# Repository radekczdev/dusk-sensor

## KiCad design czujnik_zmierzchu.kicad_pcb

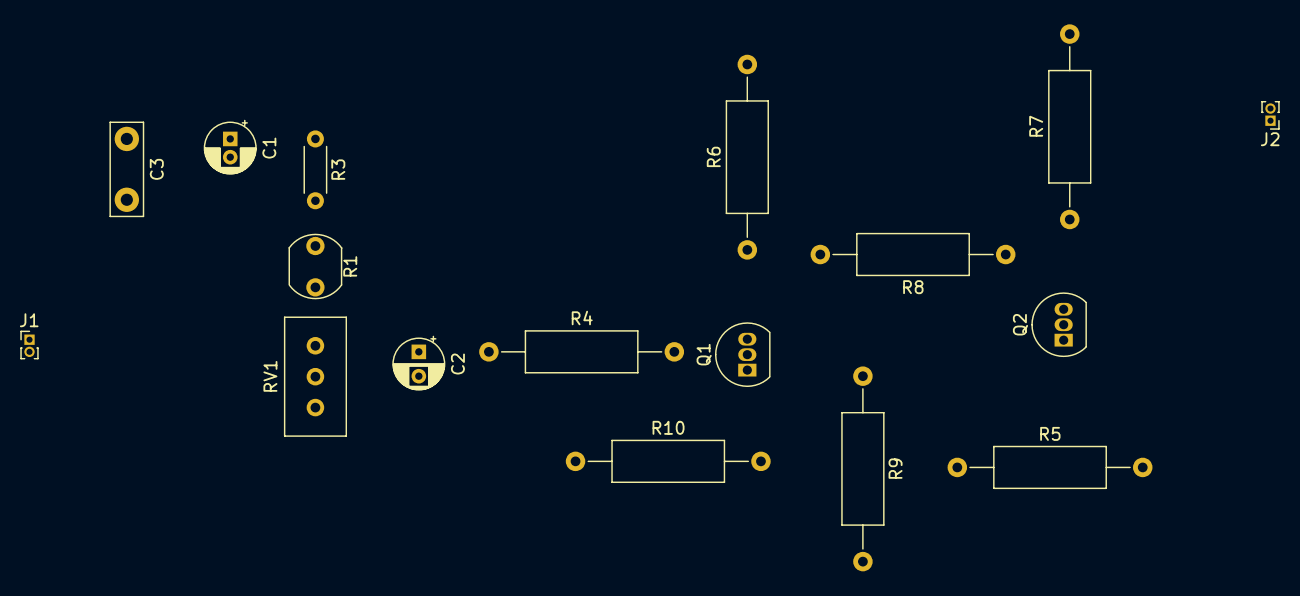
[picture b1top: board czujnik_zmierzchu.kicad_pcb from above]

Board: 2 copper layers, 17 parts (0 on the bottom side), 10 nets, no tracks yet.

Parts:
C1: 100u; CP_Radial_D4.0mm_P1.50mm
C2: 47u; CP_Radial_D4.0mm_P2.00mm
C3: 104n; C_Disc_D7.5mm_W2.5mm_P5.00mm
J1, J2: Conn_01x02_Pin; PinHeader_1x02_P1.00mm_Vertical
Q1, Q2: PN2222A; TO-92_Inline
R1: 50k; R_LDR_5.1x4.3mm_P3.4mm_Vertical
R3: 10k; R_Axial_DIN0204_L3.6mm_D1.6mm_P5.08mm_Horizontal
R4, R8: 22k; R_Axial_DIN0309_L9.0mm_D3.2mm_P15.24mm_Horizontal
R5, R10: R; R_Axial_DIN0309_L9.0mm_D3.2mm_P15.24mm_Horizontal
R6: 12k; R_Axial_DIN0309_L9.0mm_D3.2mm_P15.24mm_Horizontal
R7: 10k; R_Axial_DIN0309_L9.0mm_D3.2mm_P15.24mm_Horizontal
R9: 100; R_Axial_DIN0309_L9.0mm_D3.2mm_P15.24mm_Horizontal
RV1: 50k; Potentiometer_Bourns_3296W_Vertical

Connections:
+3.3V: C1.1, C3.1, J1.1, J2.2, R3.1, R6.2, R7.2
/Vout -: J2.1, Q2.3 (C), R5.2, R7.1
GND: C1.2, C2.2, C3.2, J1.2, R9.2, RV1.2
unnamed: C2.1, R1.2, R4.1, RV1.1
unnamed: Q1.2 (B), R4.2, R10.1
unnamed: Q1.3 (C), R6.1, R8.2
unnamed: Q1.1 (E), Q2.1 (E), R9.1
unnamed: Q2.2 (B), R8.1
unnamed: R1.1, R3.2
unnamed: R5.1, R10.2

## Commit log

2025-04-09 Dusk sensor kicad files
